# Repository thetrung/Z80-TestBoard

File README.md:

# Z80-TestBoard
Another test-NOP board for Z80 with NE555P.

### Note
A Strip-off version of Z80-Debugger but nothing rather than :
- Z80-NOP testboard for PLCC-44 package
- SOP28-DIP28 socket converter
- Tiny LED 5V power board 

### Preview 

### SilkScreen

### Schematic

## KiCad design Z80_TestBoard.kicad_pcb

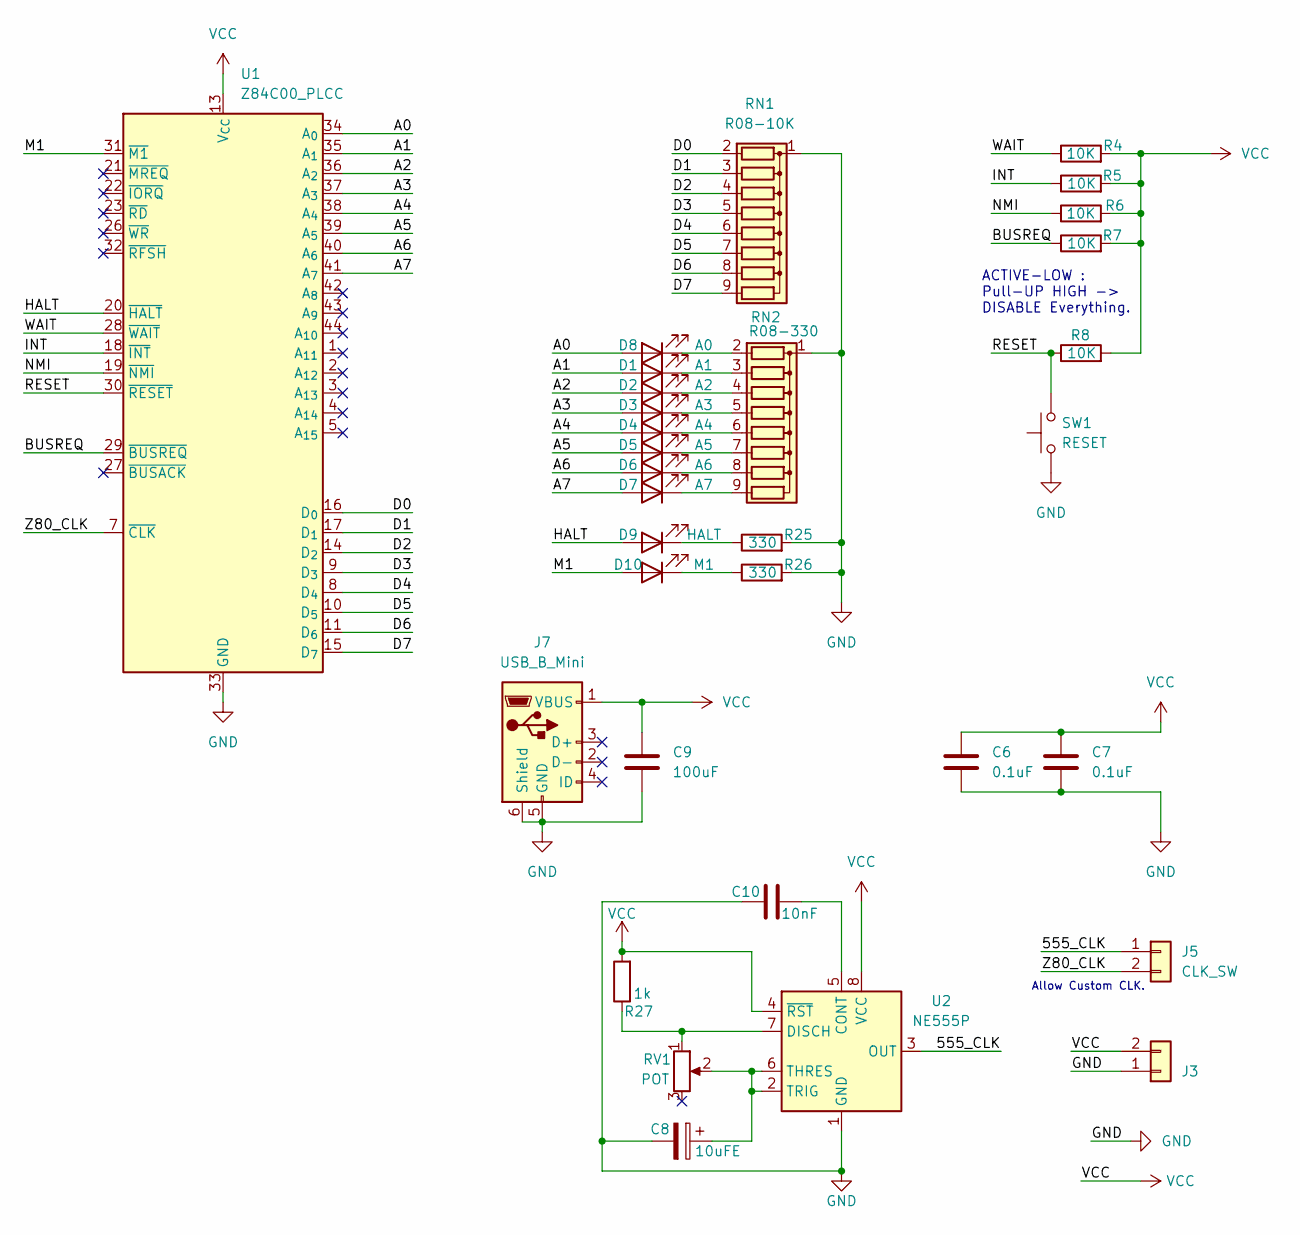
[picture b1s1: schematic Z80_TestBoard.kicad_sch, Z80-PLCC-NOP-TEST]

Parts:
C6, C7: 0.1uF; C_Disc_D3.4mm_W2.1mm_P2.50mm
C8: 10uFE; C_Radial_D4.0mm_H5.0mm_P1.50mm
C9: 100uF; C_Radial_D4.0mm_H5.0mm_P1.50mm
C10: 10nF; C_Disc_D3.4mm_W2.1mm_P2.50mm
D1: A1; LED_D3.0mm
D2: A2; LED_D3.0mm
D3: A3; LED_D3.0mm
D4: A4; LED_D3.0mm
D5: A5; LED_D3.0mm
D6: A6; LED_D3.0mm
D7: A7; LED_D3.0mm
D8: A0; LED_D3.0mm
D9: HALT; LED_D3.0mm
D10: M1; LED_D3.0mm
J3: PWR; PinHeader_1x02_P2.54mm_Vertical
J5: CLK_SW; PinHeader_1x02_P2.54mm_Vertical
J7: USB_B_Mini; USB_MINI_B_90_Angled
R4, R5, R6, R7, R8: 10K; R_Axial_DIN0207_L6.3mm_D2.5mm_P10.16mm_Horizontal
R25, R26: 330; R_Axial_DIN0207_L6.3mm_D2.5mm_P10.16mm_Horizontal
R27: 1k; R_Axial_DIN0207_L6.3mm_D2.5mm_P10.16mm_Horizontal
RN1: R08-10K; R_Array_SIP9
RN2: R08-330; R_Array_SIP9
RV1: POT; Potentiometer_Bourns_PTV09A-1_Single_Vertical
SW1: RESET; SW_PUSH_6mm
U1: Z84C00_PLCC; PLCC-44_THT-Socket
U2: NE555P; DIP-8_W7.62mm

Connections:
/Root/555_CLK: J5.1, U2.3 (OUT)
/Root/A0: D8.2 (A), U1.34 (A_{0})
/Root/A1: D1.2 (A), U1.35 (A_{1})
/Root/A2: D2.2 (A), U1.36 (A_{2})
/Root/A3: D3.2 (A), U1.37 (A_{3})
/Root/A4: D4.2 (A), U1.38 (A_{4})
/Root/A5: D5.2 (A), U1.39 (A_{5})
/Root/A6: D6.2 (A), U1.40 (A_{6})
/Root/A7: D7.2 (A), U1.41 (A_{7})
/Root/BUSREQ: R7.1, U1.29 (~BUSREQ)
/Root/D0: RN1.2 (R1), U1.16 (D_{0})
/Root/D1: RN1.3 (R2), U1.17 (D_{1})
/Root/D2: RN1.4 (R3), U1.14 (D_{2})
/Root/D3: RN1.5 (R4), U1.9 (D_{3})
/Root/D4: RN1.6 (R5), U1.8 (D_{4})
/Root/D5: RN1.7 (R6), U1.10 (D_{5})
/Root/D6: RN1.8 (R7), U1.11 (D_{6})
/Root/D7: RN1.9 (R8), U1.15 (D_{7})
/Root/HALT: D9.2 (A), U1.20 (~HALT)
/Root/INT: R5.1, U1.18 (~INT)
/Root/M1: D10.2 (A), U1.31 (~M1)
/Root/NMI: R6.1, U1.19 (~NMI)
/Root/RESET: R8.1, SW1.2, U1.30 (~RESET)
/Root/WAIT: R4.1, U1.28 (~WAIT)
/Root/Z80_CLK: J5.2, U1.7 (~CLK)
GND: C6.1, C7.1, C8.2, C9.1, C10.2, J3.1, J7.5 (GND), J7.6 (Shield), R25.2, R26.2, RN1.1 (common), RN2.1 (common), SW1.1, U1.33 (GND), U2.1 (GND)
unnamed: D1.1 (K), RN2.3 (R2)
unnamed: D2.1 (K), RN2.4 (R3)
unnamed: D3.1 (K), RN2.5 (R4)
unnamed: D4.1 (K), RN2.6 (R5)
unnamed: D5.1 (K), RN2.7 (R6)
unnamed: D6.1 (K), RN2.8 (R7)
unnamed: D7.1 (K), RN2.9 (R8)
unnamed: D8.1 (K), RN2.2 (R1)
unnamed: D9.1 (K), R25.1
unnamed: D10.1 (K), R26.1
unnamed: C10.1, U2.5 (CONT)
unnamed: R27.1, RV1.1, U2.7 (DISCH)
unnamed: C8.1, RV1.2, U2.2 (TRIG), U2.6 (THRES)
VCC: C6.2, C7.2, C9.2, J3.2, J7.1 (VBUS), R4.2, R5.2, R6.2, R7.2, R8.2, R27.2, U1.13 (V_{CC}), U2.4 (~RST), U2.8 (VCC)

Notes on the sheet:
ACTIVE-LOW : Pull-UP HIGH -> DISABLE Everything.
Allow Custom CLK.

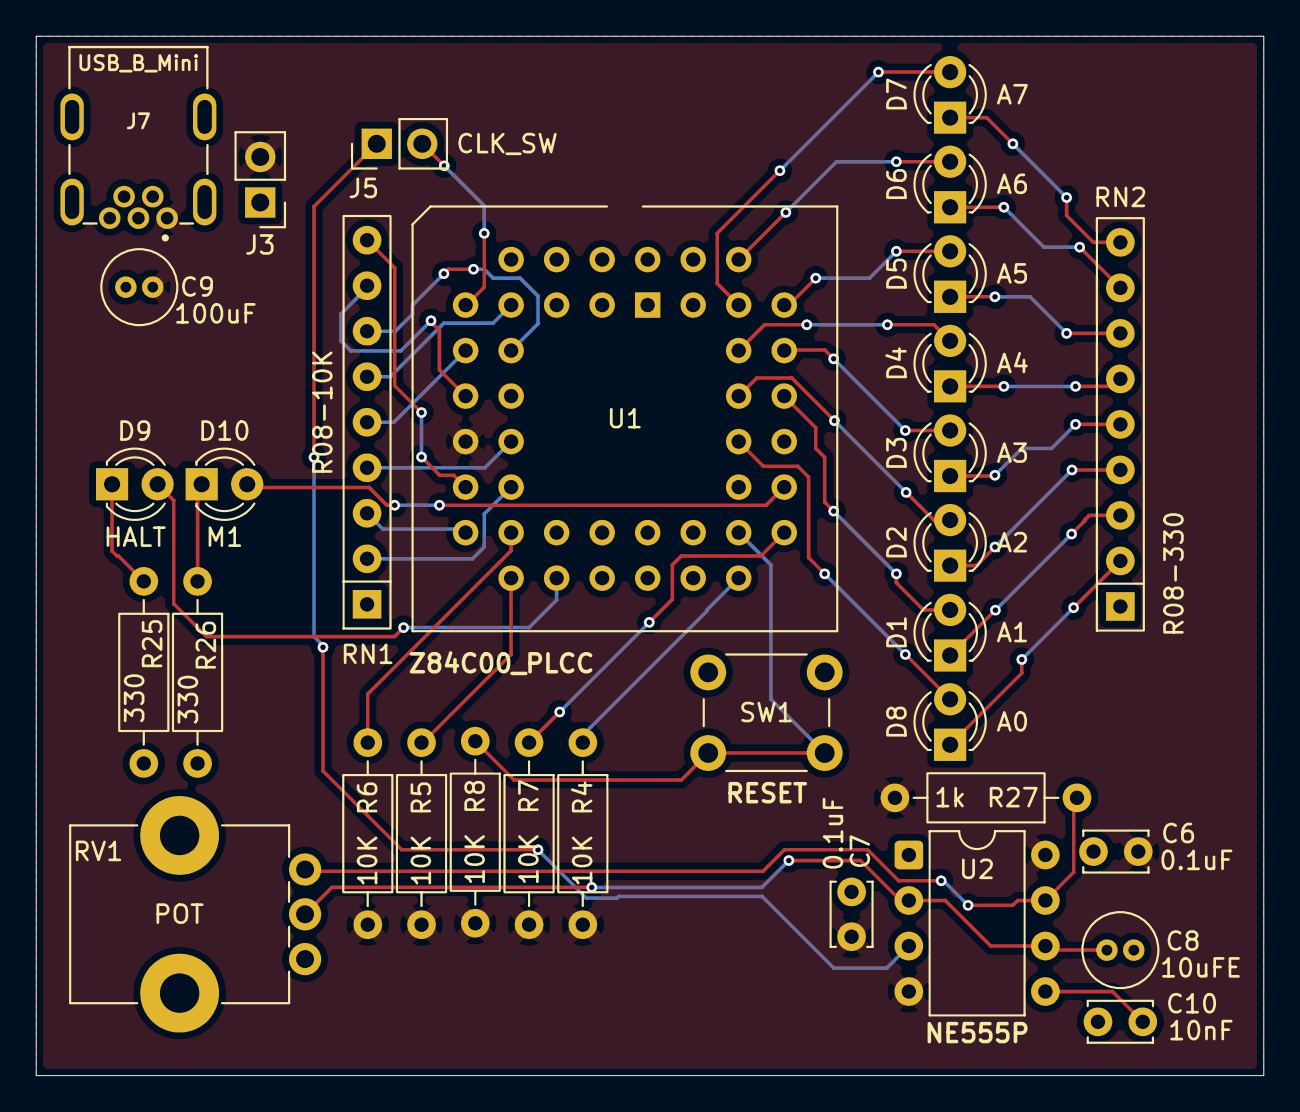
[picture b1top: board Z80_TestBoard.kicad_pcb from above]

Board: 2 copper layers, 68.5 x 58.0 mm, 32 parts (0 on the bottom side), 40 nets.
